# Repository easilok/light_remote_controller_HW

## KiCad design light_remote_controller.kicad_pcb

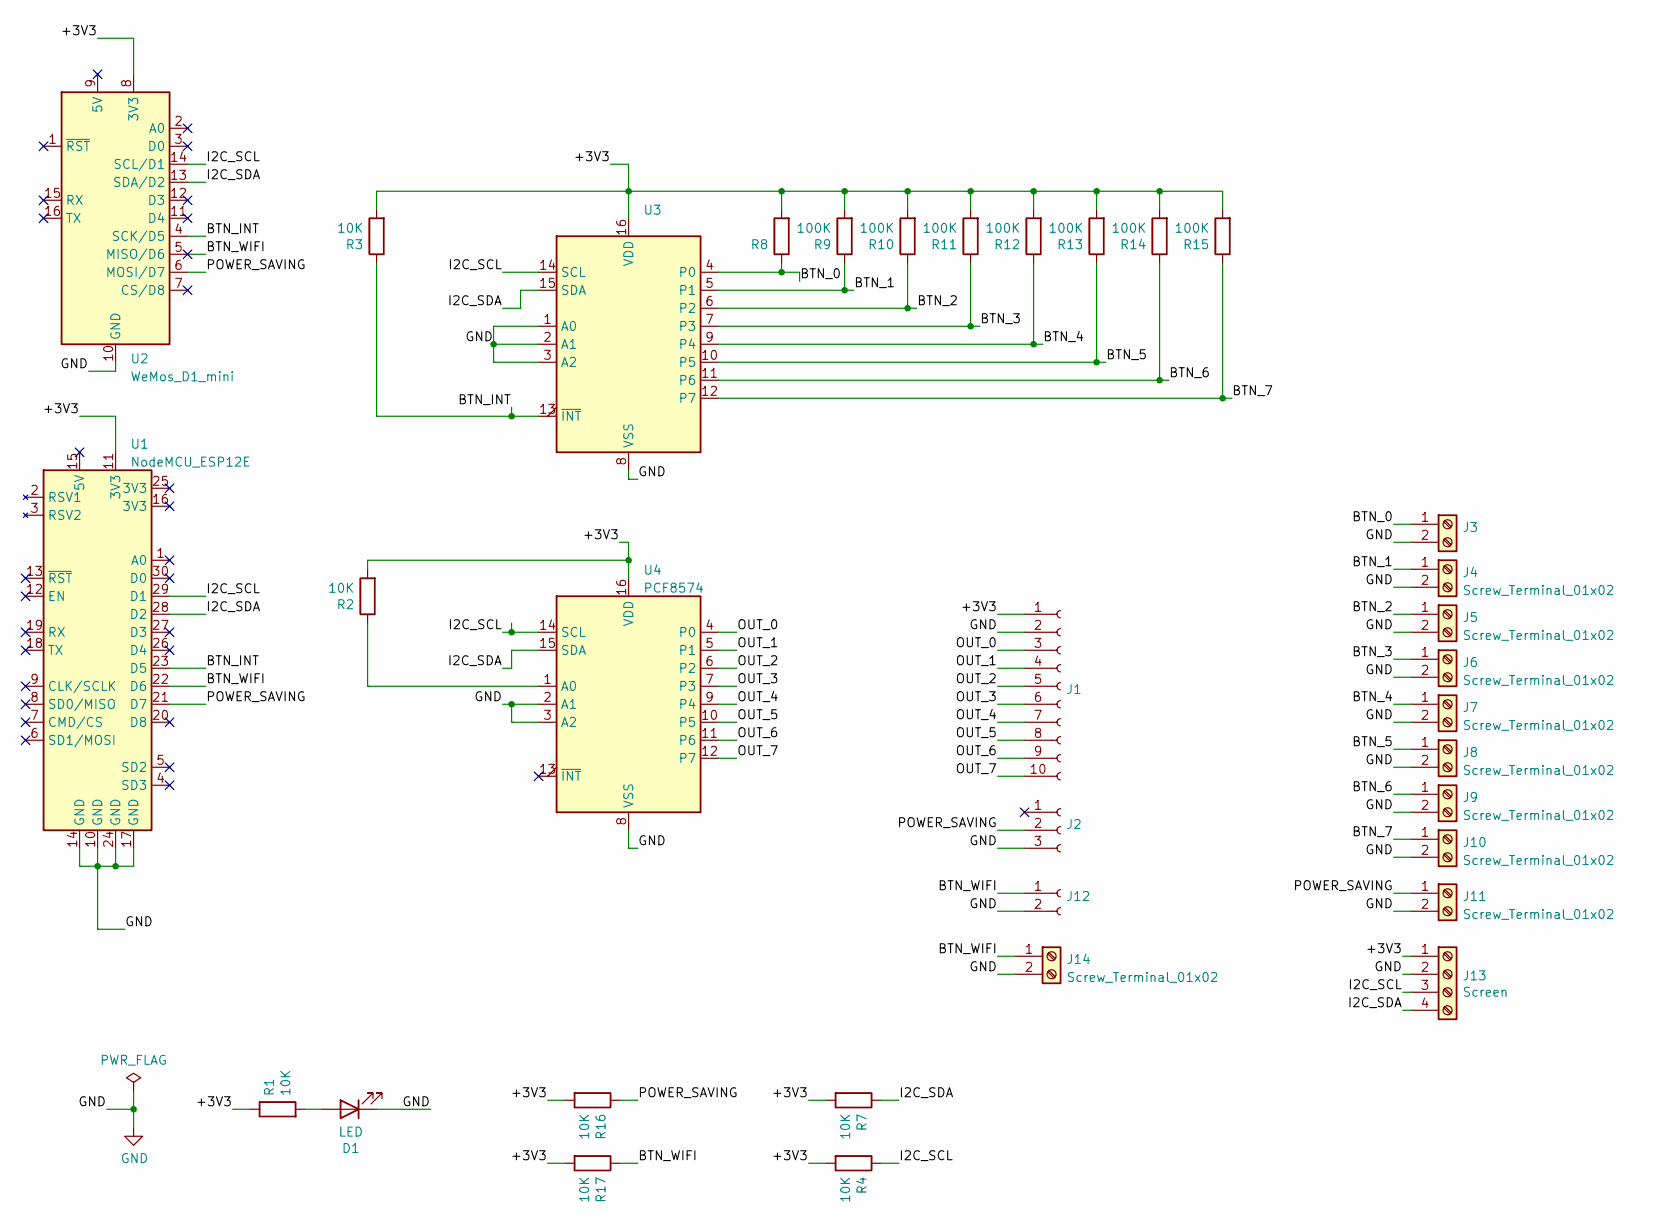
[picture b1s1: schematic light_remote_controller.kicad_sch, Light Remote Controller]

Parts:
D1: LED; LED_D3.0mm
J1, J2, J3, J12: (no value)
J4, J5, J6, J7, J8, J9, J10, J11: Screw_Terminal_01x02
J13: Screen; TerminalBlock_bornier-4_P5.08mm
J14: Screw_Terminal_01x02; TerminalBlock_bornier-2_P5.08mm
R1, R2, R3, R4, R7, R16, R17: 10K; R_0805_2012Metric
R8: (no value)
R9, R10, R11, R12, R13, R14, R15: 100K; R_0805_2012Metric
U1: NodeMCU_ESP12E; NodeMCU1.0_12-E
U2: WeMos_D1_mini; WEMOS_D1_mini_light
U3: (no value)
U4: PCF8574

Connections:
/+3V3: J1.1, J13.1, R1.1, R2.2, R3.2, R4.2, R7.2, R8.2, R9.2, R10.2, R11.2, R12.2, R13.2, R14.2, R15.2, R16.2, R17.2, U1.11 (3V3), U2.8 (3V3), U3.16 (VDD), U4.16 (VDD)
/BTN_0: J3.1, R8.1, U3.4 (P0)
/BTN_1: J4.1, R9.1, U3.5 (P1)
/BTN_2: J5.1, R10.1, U3.6 (P2)
/BTN_3: J6.1, R11.1, U3.7 (P3)
/BTN_4: J7.1, R12.1, U3.9 (P4)
/BTN_5: J8.1, R13.1, U3.10 (P5)
/BTN_6: J9.1, R14.1, U3.11 (P6)
/BTN_7: J10.1, R15.1, U3.12 (P7)
/BTN_INT: R3.1, U1.23 (D5), U2.4 (SCK/D5), U3.13 (~INT)
/BTN_WIFI: J12.1, J14.1, R17.1, U1.22 (D6), U2.5 (MISO/D6)
/I2C_SCL: J13.3, R4.1, U1.29 (D1), U2.14 (SCL/D1), U3.14 (SCL), U4.14 (SCL)
/I2C_SDA: J13.4, R7.1, U1.28 (D2), U2.13 (SDA/D2), U3.15 (SDA), U4.15 (SDA)
/OUT_0: J1.3, U4.4 (P0)
/OUT_1: J1.4, U4.5 (P1)
/OUT_2: J1.5, U4.6 (P2)
/OUT_3: J1.6, U4.7 (P3)
/OUT_4: J1.7, U4.9 (P4)
/OUT_5: J1.8, U4.10 (P5)
/OUT_6: J1.9, U4.11 (P6)
/OUT_7: J1.10, U4.12 (P7)
/POWER_SAVING: J2.2, J11.1, R16.1, U1.21 (D7), U2.6 (MOSI/D7)
GND: D1.1 (K), J1.2, J2.3, J3.2, J4.2, J5.2, J6.2, J7.2, J8.2, J9.2, J10.2, J11.2, J12.2, J13.2, J14.2, U1.10 (GND), U1.14 (GND), U1.17 (GND), U1.24 (GND), U2.10 (GND), U3.1 (A0), U3.2 (A1), U3.3 (A2), U3.8 (VSS), U4.2 (A1), U4.3 (A2), U4.8 (VSS)
unnamed: D1.2 (A), R1.2
unnamed: R2.1, U4.1 (A0)

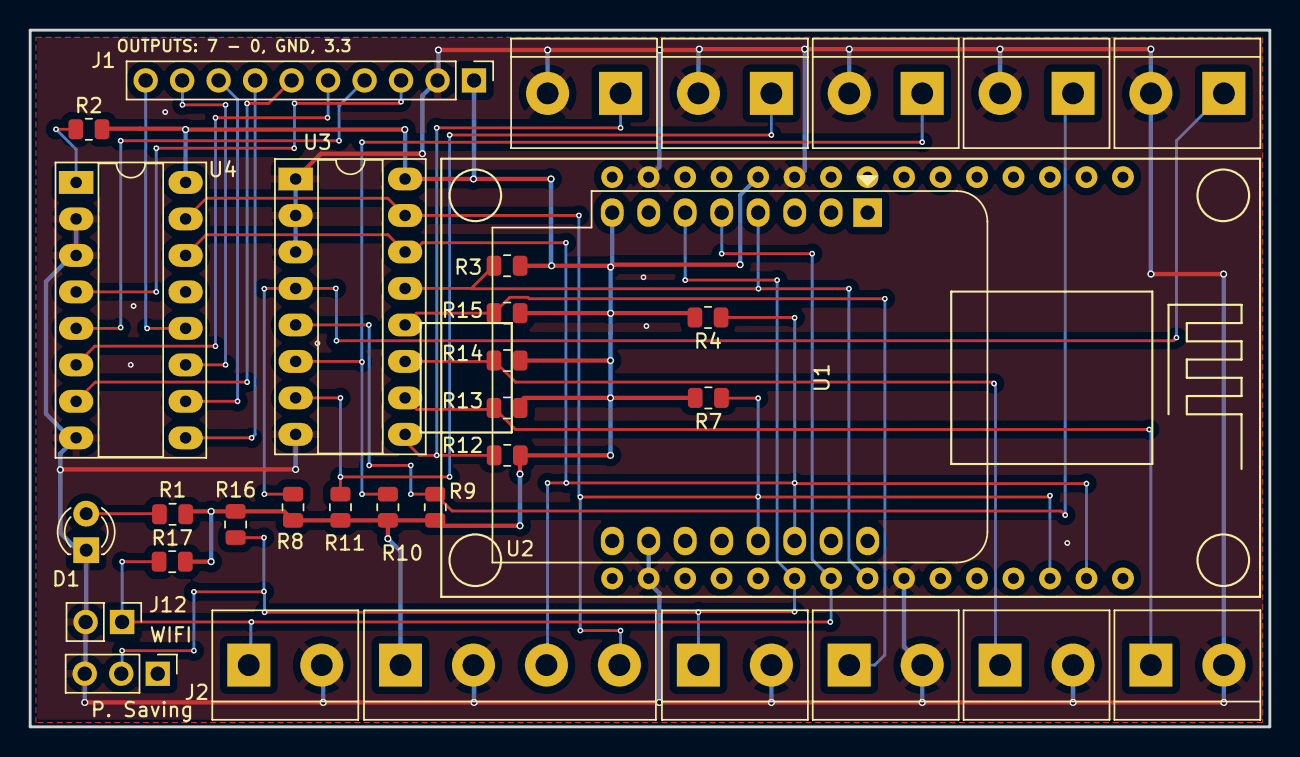
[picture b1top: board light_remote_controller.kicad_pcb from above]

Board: 2 copper layers, 86.3 x 48.5 mm, 34 parts (0 on the bottom side), 25 nets.

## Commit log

2022-05-06 Schematic ready. PCB component placement
2022-11-20 Final version that went to production
